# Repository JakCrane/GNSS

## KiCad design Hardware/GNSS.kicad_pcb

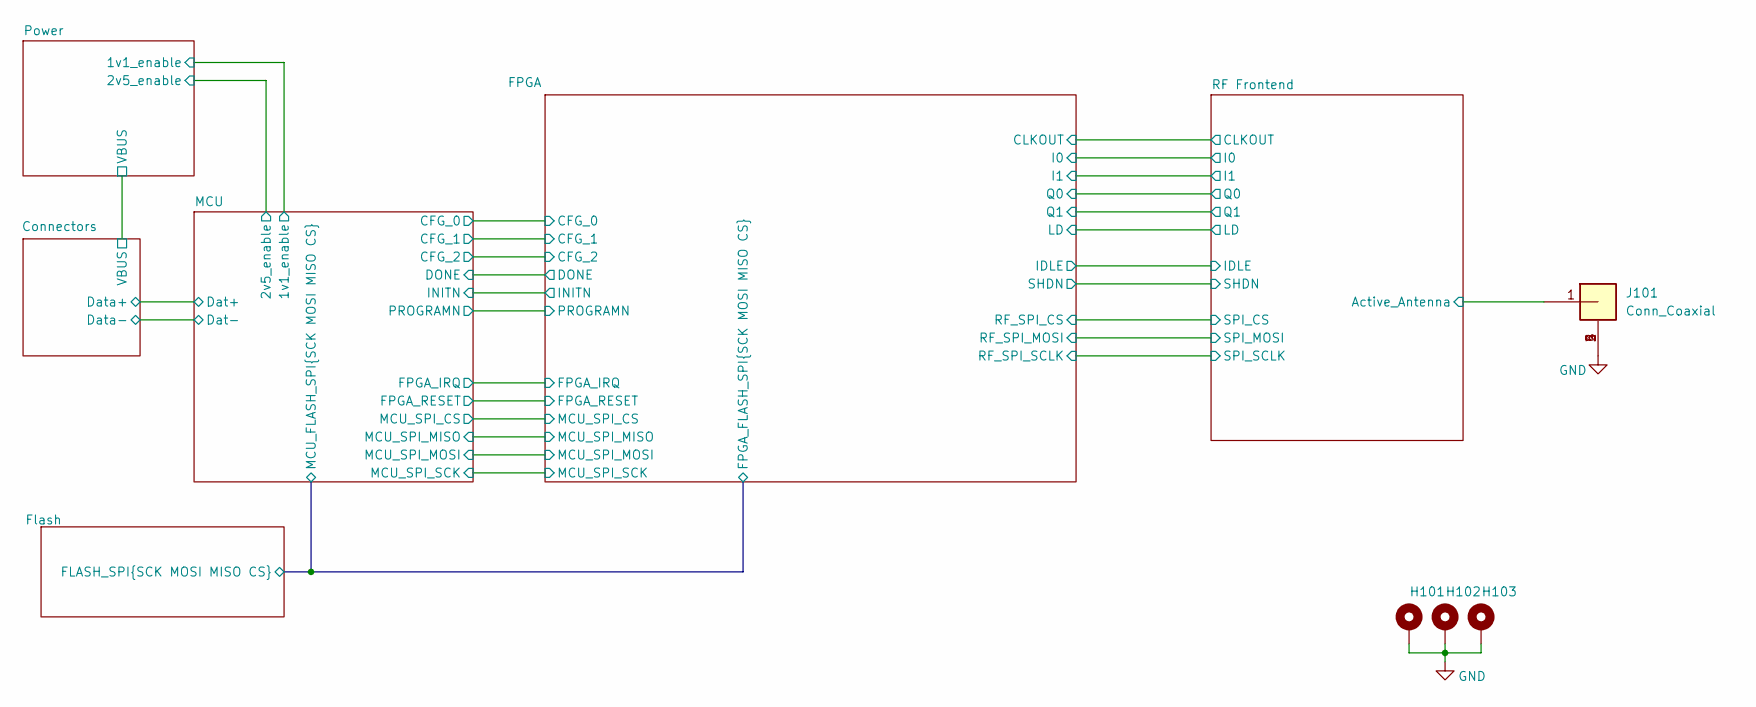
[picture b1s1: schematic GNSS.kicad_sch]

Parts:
H101, H102, H103: MountingHole_Pad; MountingHole_3.2mm_M3_Pad
J101: Conn_Coaxial; SMACONNECTOR; Mouser Part Number 471-SMACONNECTOR

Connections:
/RF Frontend/Active_Antenna: J101.1; also elsewhere on the board
GND: H101.1 (1_1), H102.1 (1_1), H103.1 (1_1), J101.2, J101.3, J101.4, J101.5; also elsewhere on the board

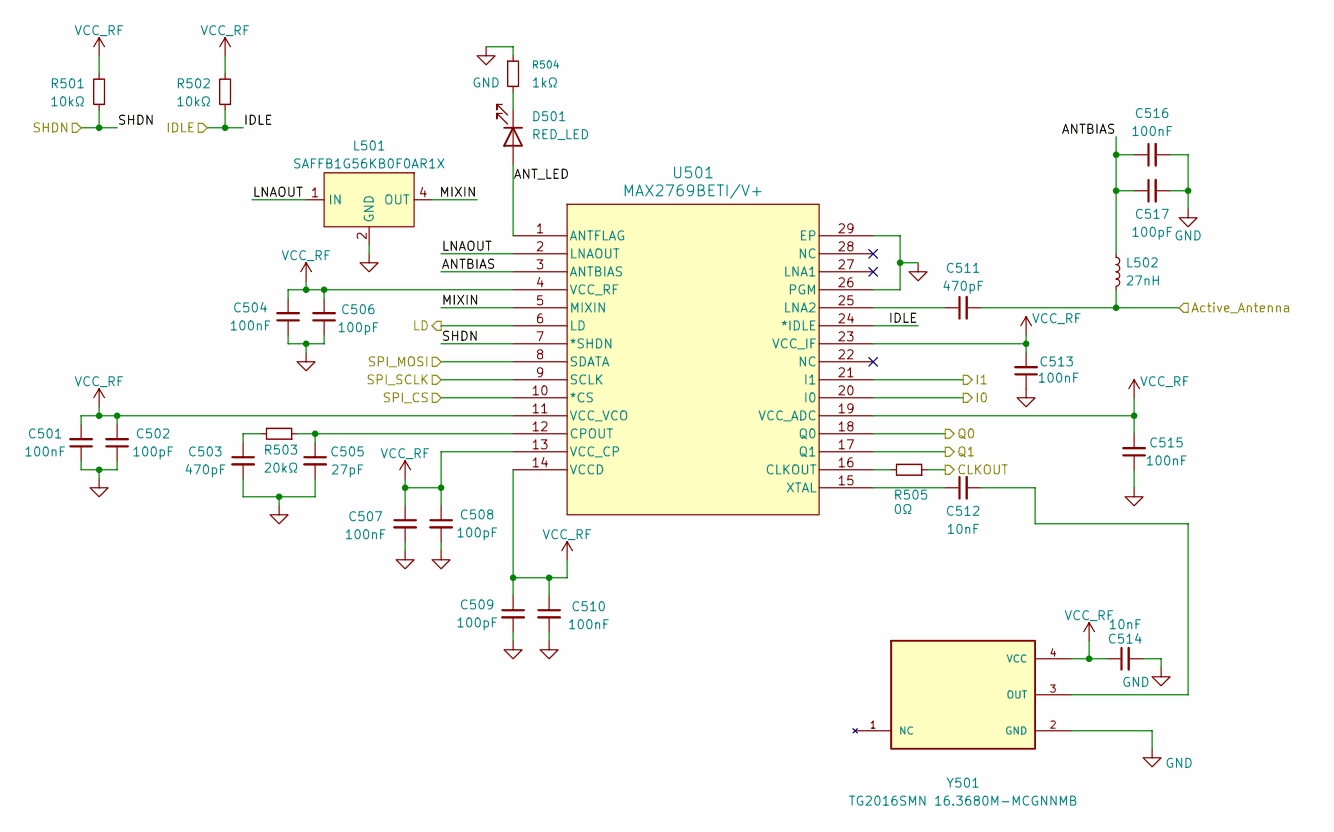
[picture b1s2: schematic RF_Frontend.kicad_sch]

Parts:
C501, C504, C507, C510, C513, C515, C516: 100nF; C_0402_1005Metric
C502, C506, C508, C509, C517: 100pF; C_0402_1005Metric
C503, C511: 470pF; C_0402_1005Metric
C505: 27pF; C_0402_1005Metric
C512, C514: 10nF; C_0402_1005Metric
D501: RED_LED; LED_0402_1005Metric
L501: SAFFB1G56KB0F0AR1X; FILTER-SMD_5P-L1.1-W0.9-L_RSFP2413E; MPN SAFFB1G56KB0F0AR1X; LCSC Part C91647
L502: 27nH; L_0402_1005Metric
R501, R502: 10kΩ; R_0402_1005Metric
R503: 20kΩ; R_0402_1005Metric
R504: 1kΩ; R_0402_1005Metric
R505: 0Ω; R_0402_1005Metric
U501: MAX2769BETI/V+; 21-0140_T2855&plus_3_MXM
Y501: TG2016SMN 16.3680M-MCGNNMB; OSC_TG2016SMN_25.0000M-ECGNNM3; PARTREV 1.3

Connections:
/FPGA/CLKOUT: R505.1; also elsewhere on the board
/FPGA/I0: U501.20 (I0); also elsewhere on the board
/FPGA/I1: U501.21 (I1); also elsewhere on the board
/FPGA/LD: U501.6 (LD); also elsewhere on the board
/FPGA/Q0: U501.18 (Q0); also elsewhere on the board
/FPGA/Q1: U501.17 (Q1); also elsewhere on the board
/FPGA/RF_SPI_CS: U501.10 (*CS); also elsewhere on the board
/FPGA/RF_SPI_MOSI: U501.8 (SDATA); also elsewhere on the board
/FPGA/RF_SPI_SCLK: U501.9 (SCLK); also elsewhere on the board
/RF Frontend/ANTBIAS: C516.1, C517.1, L502.1, U501.3 (ANTBIAS)
/RF Frontend/ANT_LED: D501.2 (A), U501.1 (ANTFLAG)
/RF Frontend/Active_Antenna: C511.2, L502.2; also elsewhere on the board
/RF Frontend/IDLE: R502.1, U501.24 (*IDLE); also elsewhere on the board
/RF Frontend/LNAOUT: L501.1 (IN), U501.2 (LNAOUT)
/RF Frontend/MIXIN: L501.4 (OUT), U501.5 (MIXIN)
/RF Frontend/SHDN: R501.1, U501.7 (*SHDN); also elsewhere on the board
GND: C501.1, C502.1, C503.2, C504.1, C505.2, C506.1, C507.2, C508.2, C509.2, C510.2, C513.1, C514.2, C515.1, C516.2, C517.2, L501.2 (GND), L501.3 (GND), L501.5 (GND), R504.1, U501.26 (PGM), U501.29 (EP), Y501.2 (GND); also elsewhere on the board
unnamed: C503.1, R503.2
unnamed: D501.1 (K), R504.2
unnamed: R505.2, U501.16 (CLKOUT)
unnamed: C505.1, R503.1, U501.12 (CPOUT)
unnamed: C511.1, U501.25 (LNA2)
unnamed: C512.1, U501.15 (XTAL)
unnamed: C512.2, Y501.3 (OUT)
VCC_RF: C501.2, C502.2, C504.2, C506.2, C507.1, C508.1, C509.1, C510.1, C513.2, C514.1, C515.2, R501.2, R502.2, U501.4 (VCC_RF), U501.11 (VCC_VCO), U501.13 (VCC_CP), U501.14 (VCCD), U501.19 (VCC_ADC), U501.23 (VCC_IF), Y501.4 (VCC); also elsewhere on the board

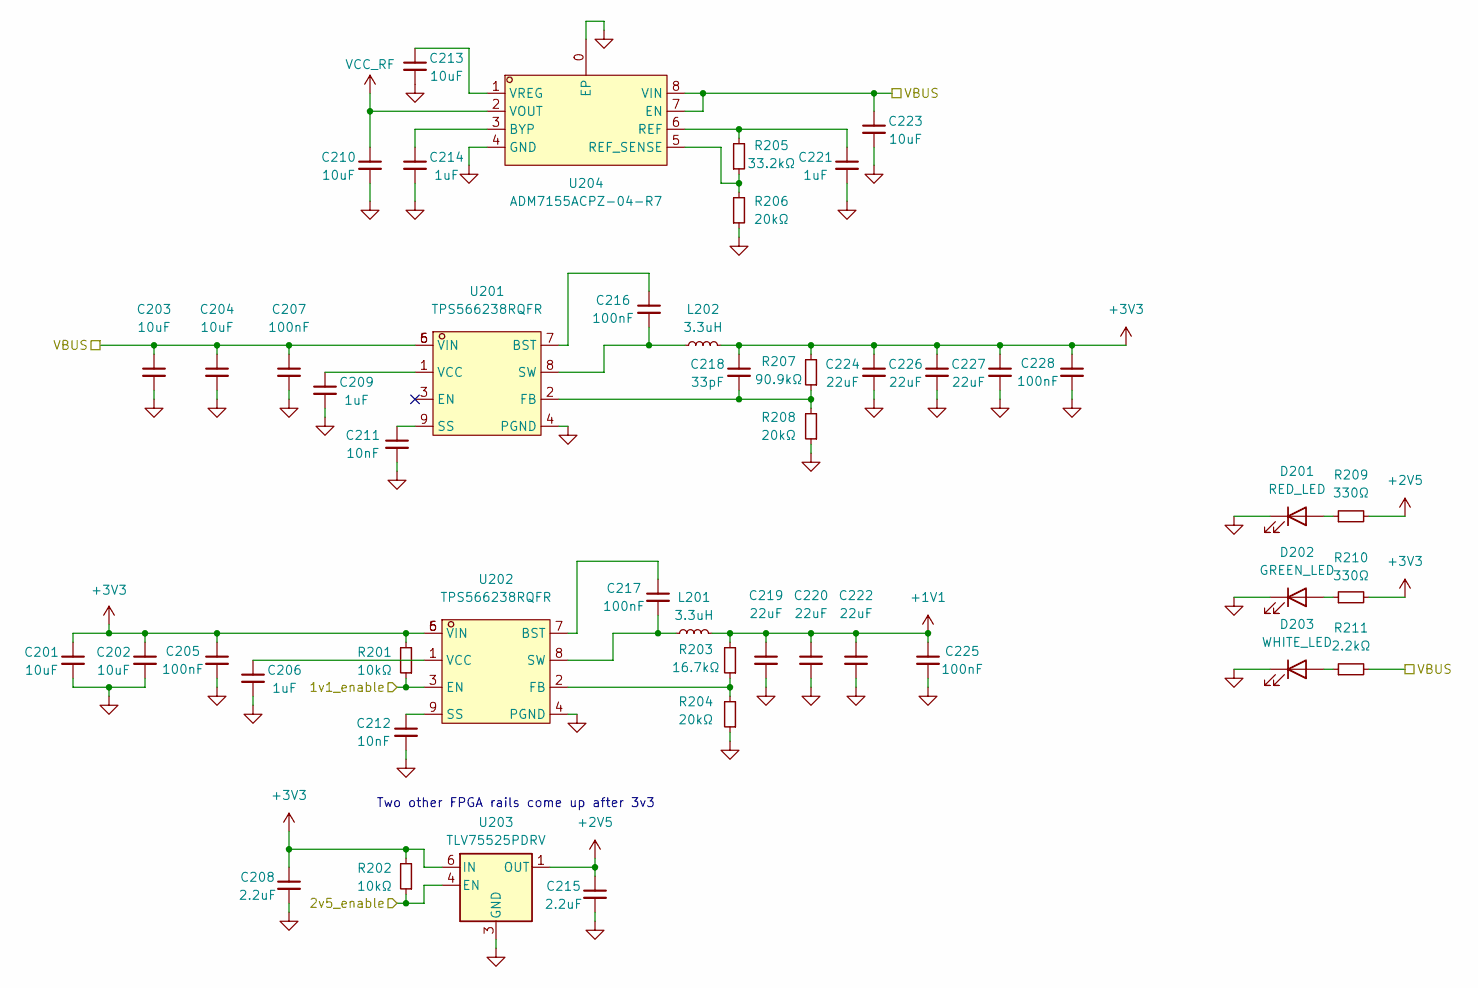
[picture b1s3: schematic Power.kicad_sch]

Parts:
C201, C202, C203, C204, C210, C213, C223: 10uF; C_0805_2012Metric
C205, C207, C216, C217, C225, C228: 100nF; C_0402_1005Metric
C206, C209, C214, C221: 1uF; C_0402_1005Metric
C208, C215: 2.2uF; C_0603_1608Metric
C211, C212: 10nF; C_0402_1005Metric
C218: 33pF; C_0402_1005Metric
C219, C220, C222, C224, C226, C227: 22uF; C_1210_3225Metric
D201: RED_LED; LED_0402_1005Metric
D202: GREEN_LED; LED_0402_1005Metric
D203: WHITE_LED; LED_0402_1005Metric
L201, L202: 3.3uH; L_Wurth_WE-HEPA-5030
R201, R202: 10kΩ; R_0402_1005Metric
R203: 16.7kΩ; R_0402_1005Metric
R204, R206, R208: 20kΩ; R_0402_1005Metric
R205: 33.2kΩ; R_0402_1005Metric
R207: 90.9kΩ; R_0402_1005Metric
R209, R210: 330Ω; R_0402_1005Metric
R211: 2.2kΩ; R_0402_1005Metric
U201, U202: TPS566238RQFR; VQFN-HR-9_2.0-W1.5-P0.5-TL_TI_RQF0009A; MPN TPS566238RQFR; LCSC Part C5219353
U203: TLV75525PDRV; WSON-6-1EP_2x2mm_P0.65mm_EP1x1.6mm
U204: ADM7155ACPZ-04-R7; LFCSP-8_L3.0-W3.0-P0.50-BL-EP; MPN ADM7155ACPZ-04-R7; LCSC Part C209548

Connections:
+1V1: C219.1, C220.1, C222.1, C225.1, L201.2, R203.2; also elsewhere on the board
+2V5: C215.1, R209.2, U203.1 (OUT); also elsewhere on the board
+3V3: C201.1, C202.1, C205.1, C208.1, C218.1, C224.1, C226.1, C227.1, C228.1, L202.2, R201.2, R202.2, R207.2, R210.2, U202.5 (VIN), U202.6 (VIN), U203.6 (IN); also elsewhere on the board
/Connectors/VBUS: C203.1, C204.1, C207.1, C223.1, R211.2, U201.5 (VIN), U201.6 (VIN), U204.7 (EN), U204.8 (VIN); also elsewhere on the board
/MCU/1v1_enable: R201.1, U202.3 (EN); also elsewhere on the board
/MCU/2v5_enable: R202.1, U203.4 (EN); also elsewhere on the board
GND: C201.2, C202.2, C203.2, C204.2, C205.2, C206.2, C207.2, C208.2, C209.2, C210.2, C211.2, C212.2, C213.2, C214.2, C215.2, C219.2, C220.2, C221.2, C222.2, C223.2, C224.2, C225.2, C226.2, C227.2, C228.2, D201.1 (K), D202.1 (K), D203.1 (K), R204.1, R206.1, R208.1, U201.4 (PGND), U202.4 (PGND), U203.2 (NC), U203.3 (GND), U203.5 (NC), U203.7 (GND), U204.0 (EP), U204.4 (GND); also elsewhere on the board
unnamed: D201.2 (A), R209.1
unnamed: D202.2 (A), R210.1
unnamed: D203.2 (A), R211.1
unnamed: C216.1, U201.7 (BST)
unnamed: C218.2, R207.1, R208.2, U201.2 (FB)
unnamed: C211.1, U201.9 (SS)
unnamed: C216.2, L202.1, U201.8 (SW)
unnamed: C209.1, U201.1 (VCC)
unnamed: C217.1, U202.7 (BST)
unnamed: R203.1, R204.2, U202.2 (FB)
unnamed: C212.1, U202.9 (SS)
unnamed: C217.2, L201.1, U202.8 (SW)
unnamed: C206.1, U202.1 (VCC)
unnamed: C214.1, U204.3 (BYP)
unnamed: C221.1, R205.2, U204.6 (REF)
unnamed: R205.1, R206.2, U204.5 (REF_SENSE)
unnamed: C213.1, U204.1 (VREG)
VCC_RF: C210.1, U204.2 (VOUT); also elsewhere on the board

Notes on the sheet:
Two other FPGA rails come up after 3v3

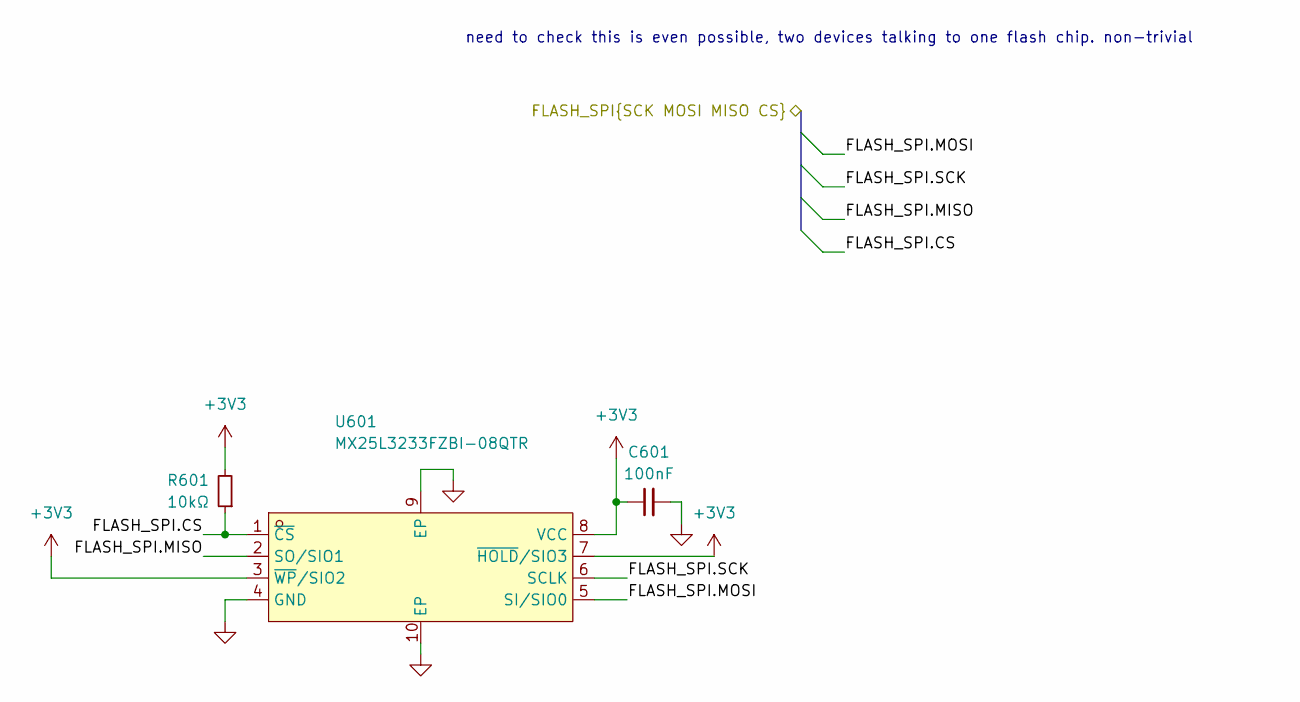
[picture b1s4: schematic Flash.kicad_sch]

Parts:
C601: 100nF; C_0402_1005Metric
R601: 10kΩ; R_0402_1005Metric
U601: MX25L3233FZBI-08QTR; USON-8_L4.0-W3.0-P0.80-BL_IS25WP032D; MPN MX25L3233FZBI-08QTR; LCSC Part C2803002

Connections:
+3V3: C601.1, R601.2, U601.3 (~WP/SIO2), U601.7 (~HOLD/SIO3), U601.8 (VCC); also elsewhere on the board
/FPGA/FPGA_FLASH_SPI.CS: R601.1, U601.1 (~CS); also elsewhere on the board
/FPGA/FPGA_FLASH_SPI.MISO: U601.2 (SO/SIO1); also elsewhere on the board
/FPGA/FPGA_FLASH_SPI.MOSI: U601.5 (SI/SIO0); also elsewhere on the board
/FPGA/FPGA_FLASH_SPI.SCK: U601.6 (SCLK); also elsewhere on the board
GND: C601.2, U601.4 (GND), U601.9 (EP), U601.10 (EP); also elsewhere on the board

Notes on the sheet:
need to check this is even possible, two devices talking to one flash chip. non-trivial

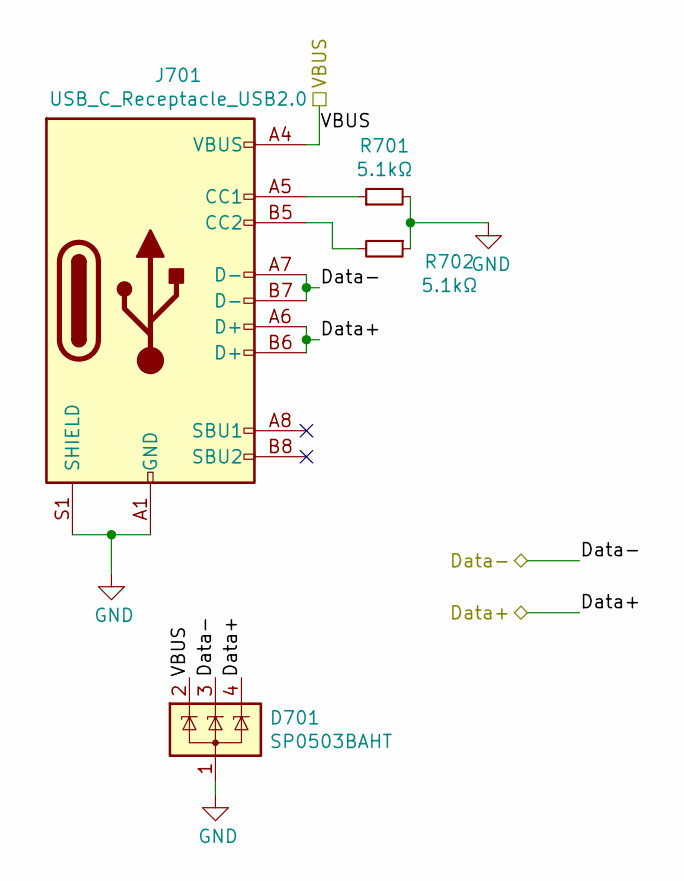
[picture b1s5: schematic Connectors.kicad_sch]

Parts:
D701: SP0503BAHT; SOT-143
J701: USB_C_Receptacle_USB2.0; USB_C_Receptacle_Palconn_UTC16-G
R701, R702: 5.1kΩ; R_0402_1005Metric

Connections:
/Connectors/Data+: D701.4 (K), J701.A6 (D+), J701.B6 (D+); also elsewhere on the board
/Connectors/Data-: D701.3 (K), J701.A7 (D-), J701.B7 (D-); also elsewhere on the board
/Connectors/VBUS: D701.2 (K), J701.A4 (VBUS), J701.A9 (VBUS), J701.B4 (VBUS), J701.B9 (VBUS); also elsewhere on the board
GND: D701.1 (A), J701.A1 (GND), J701.A12 (GND), J701.B1 (GND), J701.B12 (GND), J701.S1 (SHIELD), R701.2, R702.1; also elsewhere on the board
unnamed: J701.A5 (CC1), R701.1
unnamed: J701.B5 (CC2), R702.2

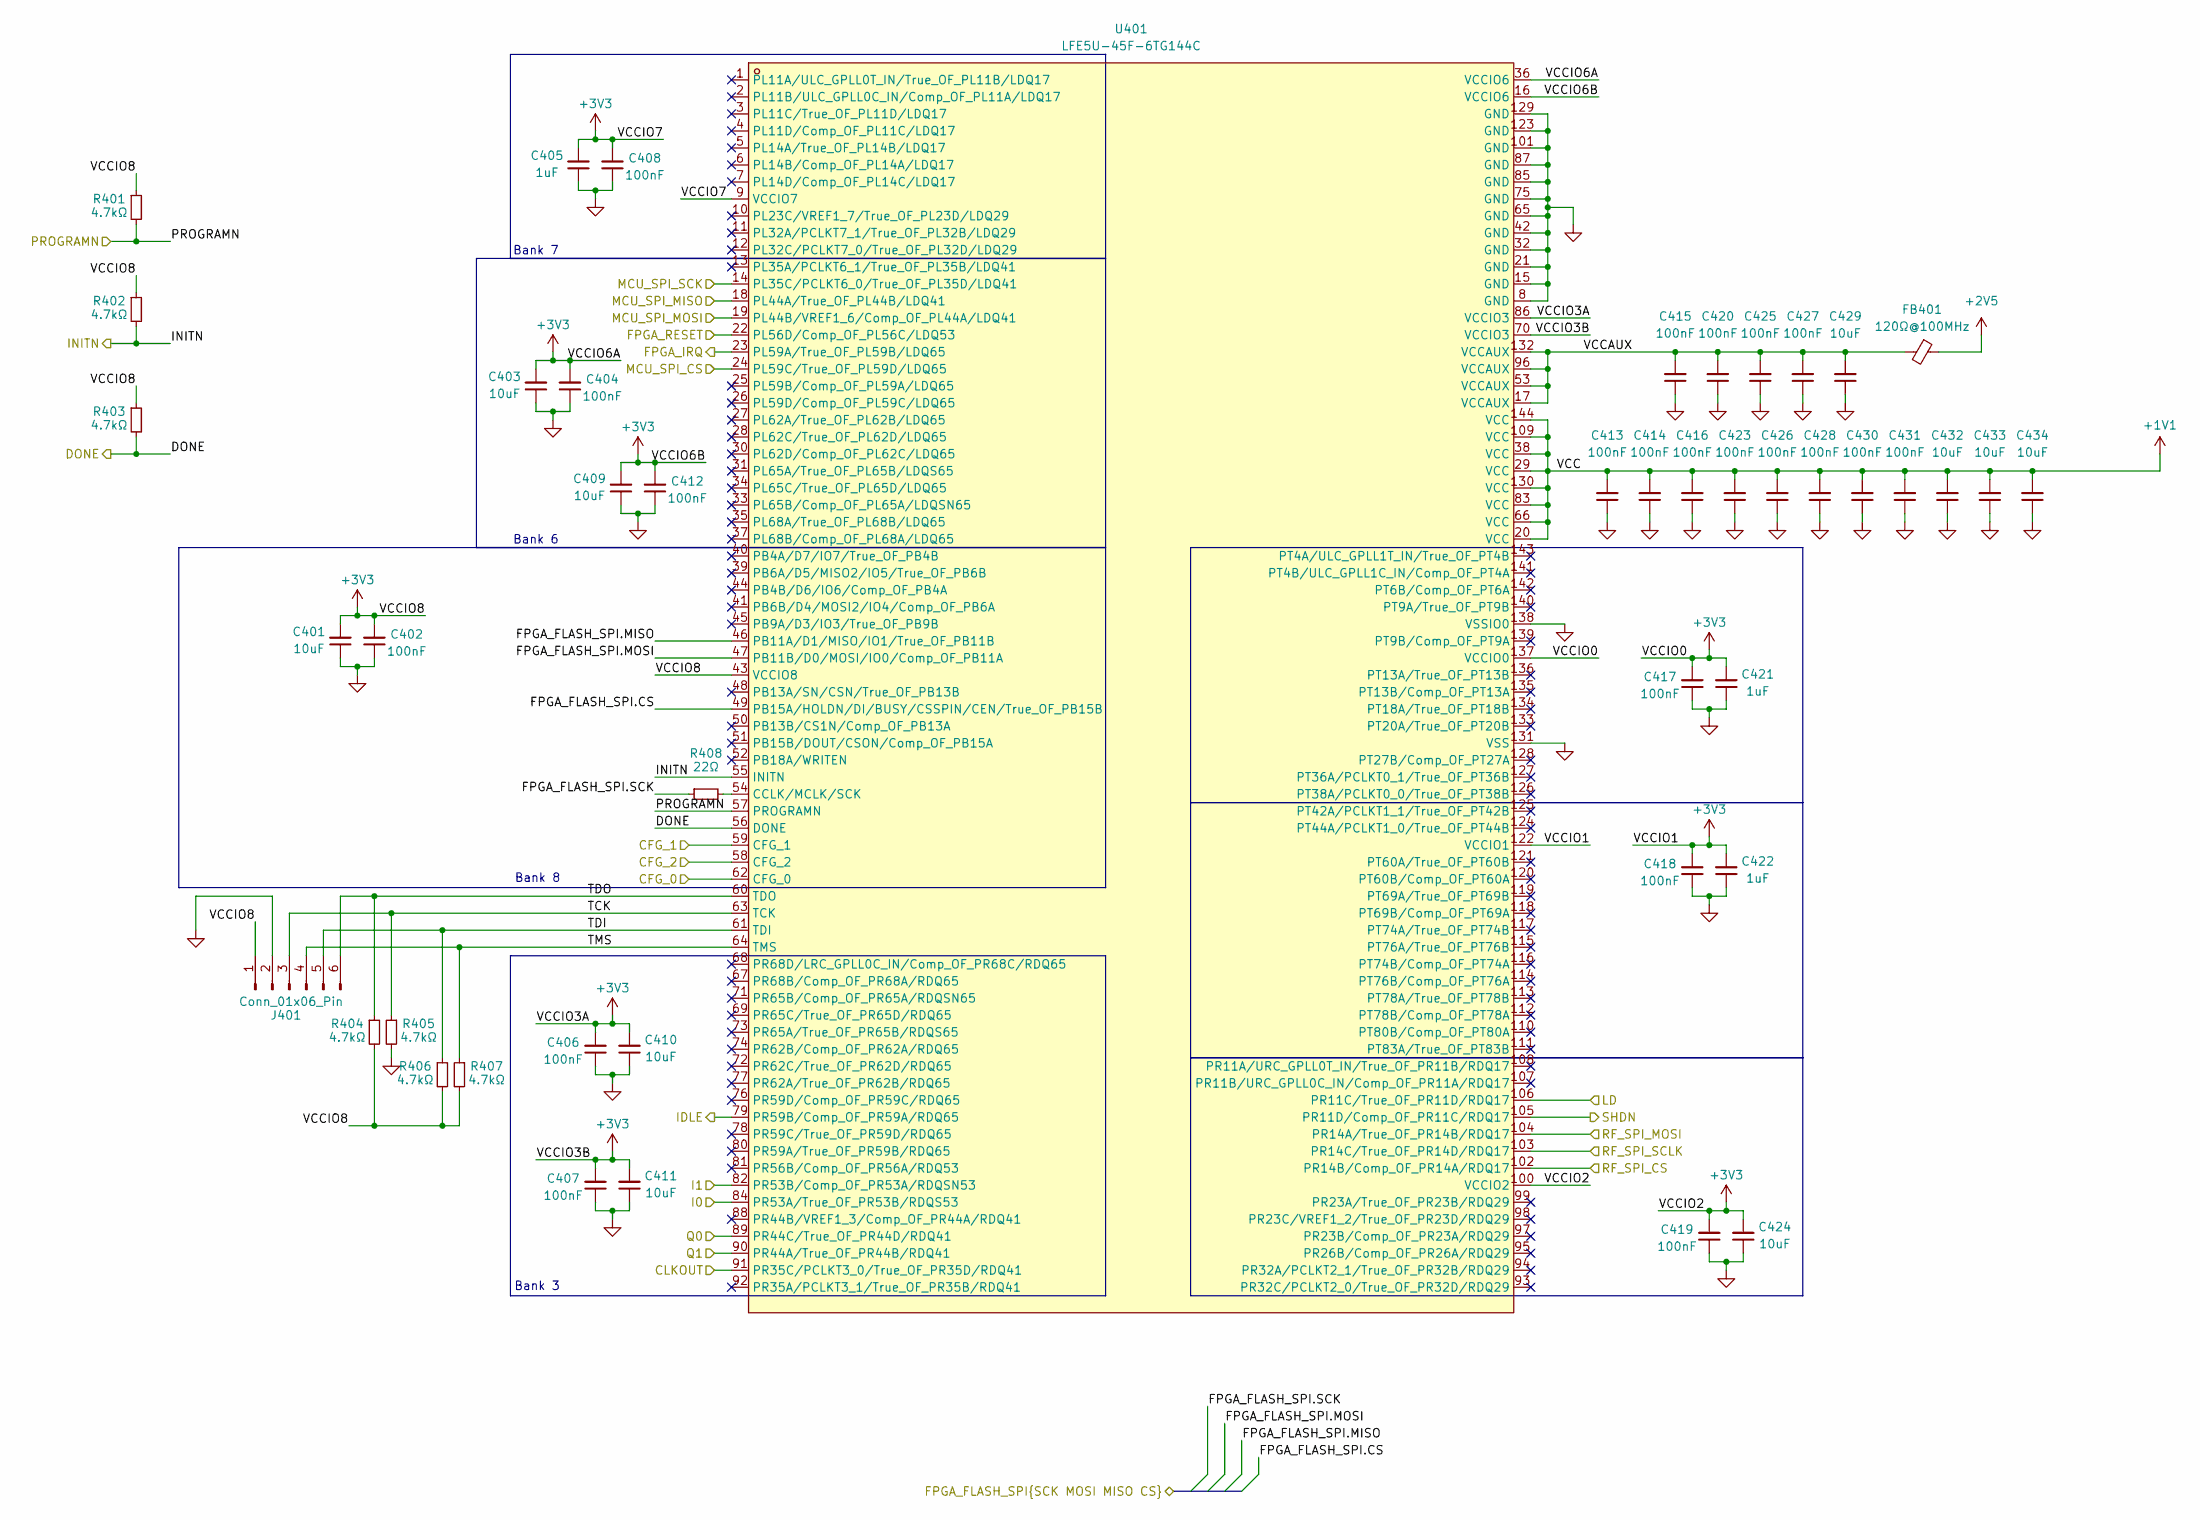
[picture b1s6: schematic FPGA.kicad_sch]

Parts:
C401, C403, C409, C410, C411, C424, C429, C432, C433, C434: 10uF; C_0805_2012Metric
C402, C404, C406, C407, C408, C412, C413, C414, C415, C416, C417, C418, C419, C420, C423, C425, C426, C427, C428, C430, C431: 100nF; C_0402_1005Metric
C405, C421, C422: 1uF; C_0402_1005Metric
FB401: 120Ω@100MHz; L_0603_1608Metric
J401: Conn_01x06_Pin; Molex_Nano-Fit_105313-xx06_1x06_P2.50mm_Horizontal
R401, R402, R403, R404, R405, R406, R407: 4.7kΩ; R_0402_1005Metric
R408: 22Ω; R_0402_1005Metric
U401: LFE5U-45F-6TG144C; TQFP-144_L20.0-W20.0-P0.50-LS22.0-TL; MPN LFE5U-45F-6TG144C; LCSC Part C19979193

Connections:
+1V1: C413.2, C414.2, C416.2, C423.2, C426.2, C428.2, C430.2, C431.2, C432.2, C433.2, C434.2, U401.20 (VCC), U401.29 (VCC), U401.38 (VCC), U401.66 (VCC), U401.83 (VCC), U401.109 (VCC), U401.130 (VCC), U401.144 (VCC); also elsewhere on the board
+2V5: FB401.1; also elsewhere on the board
+3V3: C401.2, C402.2, C403.2, C404.2, C405.2, C406.2, C407.2, C408.2, C409.2, C410.2, C411.2, C412.2, C417.2, C418.2, C419.2, C421.2, C422.2, C424.2, J401.1, R401.1, R402.1, R403.1, R404.2, R406.2, R407.2, U401.9 (VCCIO7), U401.16 (VCCIO6), U401.36 (VCCIO6), U401.43 (VCCIO8), U401.70 (VCCIO3), U401.86 (VCCIO3), U401.100 (VCCIO2), U401.122 (VCCIO1), U401.137 (VCCIO0); also elsewhere on the board
/FPGA/CFG_0: U401.62 (CFG_0); also elsewhere on the board
/FPGA/CFG_1: U401.59 (CFG_1); also elsewhere on the board
/FPGA/CFG_2: U401.58 (CFG_2); also elsewhere on the board
/FPGA/CLKOUT: U401.91 (PR35C/PCLKT3_0/True_OF_PR35D/RDQ41); also elsewhere on the board
/FPGA/DONE: R403.2, U401.56 (DONE); also elsewhere on the board
/FPGA/FPGA_FLASH_SPI.CS: U401.49 (PB15A/HOLDN/DI/BUSY/CSSPIN/CEN/True_OF_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); also elsewhere on the board
/FPGA/FPGA_FLASH_SPI.MISO: U401.46 (PB11A/D1/MISO/IO1/True_OF_PB11B); also elsewhere on the board
/FPGA/FPGA_FLASH_SPI.MOSI: U401.47 (PB11B/D0/MOSI/IO0/Comp_OF_PB11A); also elsewhere on the board
/FPGA/FPGA_FLASH_SPI.SCK: R408.1; also elsewhere on the board
/FPGA/FPGA_IRQ: U401.23 (PL59A/True_OF_PL59B/LDQ65); also elsewhere on the board
/FPGA/FPGA_RESET: U401.22 (PL56D/Comp_OF_PL56C/LDQ53); also elsewhere on the board
/FPGA/I0: U401.84 (PR53A/True_OF_PR53B/RDQS53); also elsewhere on the board
/FPGA/I1: U401.82 (PR53B/Comp_OF_PR53A/RDQSN53); also elsewhere on the board
/FPGA/INITN: R402.2, U401.55 (INITN); also elsewhere on the board
/FPGA/LD: U401.106 (PR11C/True_OF_PR11D/RDQ17); also elsewhere on the board
/FPGA/MCU_SPI_CS: U401.24 (PL59C/True_OF_PL59D/LDQ65); also elsewhere on the board
/FPGA/MCU_SPI_MISO: U401.18 (PL44A/True_OF_PL44B/LDQ41); also elsewhere on the board
/FPGA/MCU_SPI_MOSI: U401.19 (PL44B/VREF1_6/Comp_OF_PL44A/LDQ41); also elsewhere on the board
/FPGA/MCU_SPI_SCK: U401.14 (PL35C/PCLKT6_0/True_OF_PL35D/LDQ41); also elsewhere on the board
/FPGA/PROGRAMN: R401.2, U401.57 (PROGRAMN); also elsewhere on the board
/FPGA/Q0: U401.89 (PR44C/True_OF_PR44D/RDQ41); also elsewhere on the board
/FPGA/Q1: U401.90 (PR44A/True_OF_PR44B/RDQ41); also elsewhere on the board
/FPGA/RF_SPI_CS: U401.102 (PR14B/Comp_OF_PR14A/RDQ17); also elsewhere on the board
/FPGA/RF_SPI_MOSI: U401.104 (PR14A/True_OF_PR14B/RDQ17); also elsewhere on the board
/FPGA/RF_SPI_SCLK: U401.103 (PR14C/True_OF_PR14D/RDQ17); also elsewhere on the board
/FPGA/TCK: J401.3, R405.1, U401.63 (TCK)
/FPGA/TDI: J401.5, R406.1, U401.61 (TDI)
/FPGA/TDO: J401.6, R404.1, U401.60 (TDO)
/FPGA/TMS: J401.4, R407.1, U401.64 (TMS)
/FPGA/VCCAUX: C415.2, C420.2, C425.2, C427.2, C429.2, FB401.2, U401.17 (VCCAUX), U401.53 (VCCAUX), U401.96 (VCCAUX), U401.132 (VCCAUX)
/RF Frontend/IDLE: U401.79 (PR59B/Comp_OF_PR59A/RDQ65); also elsewhere on the board
/RF Frontend/SHDN: U401.105 (PR11D/Comp_OF_PR11C/RDQ17); also elsewhere on the board
GND: C401.1, C402.1, C403.1, C404.1, C405.1, C406.1, C407.1, C408.1, C409.1, C410.1, C411.1, C412.1, C413.1, C414.1, C415.1, C416.1, C417.1, C418.1, C419.1, C420.1, C421.1, C422.1, C423.1, C424.1, C425.1, C426.1, C427.1, C428.1, C429.1, C430.1, C431.1, C432.1, C433.1, C434.1, J401.2, R405.2, U401.8 (GND), U401.15 (GND), U401.21 (GND), U401.32 (GND), U401.42 (GND), U401.65 (GND), U401.75 (GND), U401.85 (GND), U401.87 (GND), U401.101 (GND), U401.123 (GND), U401.129 (GND), U401.131 (VSS), U401.138 (VSSIO0); also elsewhere on the board
unnamed: R408.2, U401.54 (CCLK/MCLK/SCK)

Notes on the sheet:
Bank 3
Bank 8
Bank 6
Bank 7

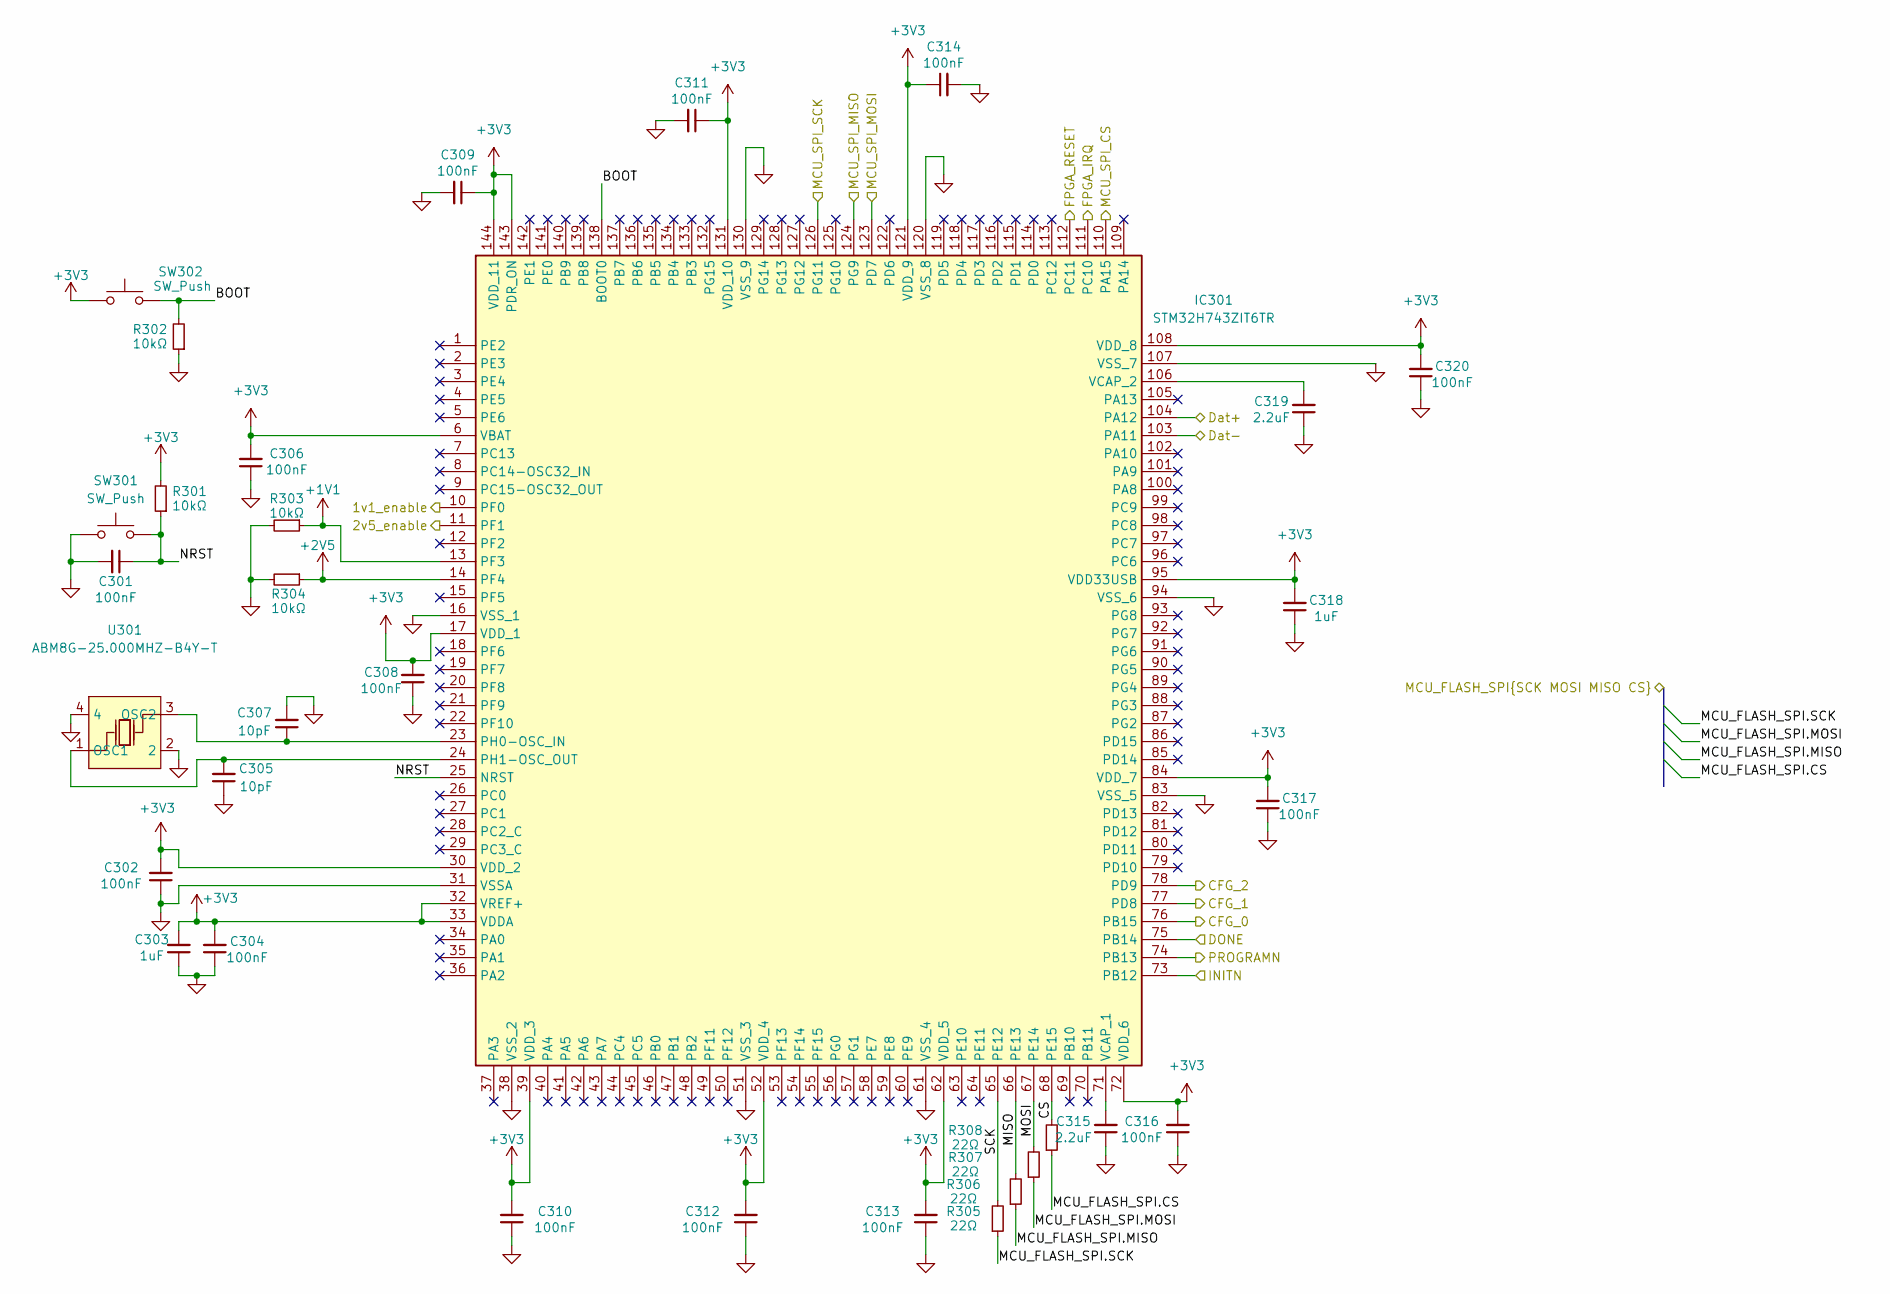
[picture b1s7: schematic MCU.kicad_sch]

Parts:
C301, C302, C304, C306, C308, C309, C310, C311, C312, C313, C314, C316, C317, C320: 100nF; C_0402_1005Metric
C303, C318: 1uF; C_0402_1005Metric
C305, C307: 10pF; C_0402_1005Metric
C315, C319: 2.2uF; C_0603_1608Metric
IC301: STM32H743ZIT6TR; QFP50P2200X2200X160-144N; Mouser Part Number 511-STM32H743ZIT6TR
R301, R302, R303, R304: 10kΩ; R_0402_1005Metric
R305, R306, R307, R308: 22Ω; R_0402_1005Metric
SW301, SW302: SW_Push; PinHeader_1x02_P2.54mm_Vertical
U301: ABM8G-25.000MHZ-B4Y-T; CRYSTAL-SMD_4P-L3.2-W2.5-TR; MPN ABM8G-25.000MHZ-B4Y-T; LCSC Part C596913

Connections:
+1V1: IC301.13 (PF3), R303.1; also elsewhere on the board
+2V5: IC301.14 (PF4), R304.1; also elsewhere on the board
+3V3: C302.2, C303.2, C304.2, C306.2, C308.2, C309.1, C310.2, C311.1, C312.2, C313.2, C314.1, C316.2, C317.2, C318.2, C320.2, IC301.6 (VBAT), IC301.17 (VDD_1), IC301.30 (VDD_2), IC301.32 (VREF+), IC301.33 (VDDA), IC301.39 (VDD_3), IC301.52 (VDD_4), IC301.62 (VDD_5), IC301.72 (VDD_6), IC301.84 (VDD_7), IC301.95 (VDD33USB), IC301.108 (VDD_8), IC301.121 (VDD_9), IC301.131 (VDD_10), IC301.143 (PDR_ON), IC301.144 (VDD_11), R301.2, SW302.1; also elsewhere on the board
/Connectors/Data+: IC301.104 (PA12); also elsewhere on the board
/Connectors/Data-: IC301.103 (PA11); also elsewhere on the board
/FPGA/CFG_0: IC301.76 (PB15); also elsewhere on the board
/FPGA/CFG_1: IC301.77 (PD8); also elsewhere on the board
/FPGA/CFG_2: IC301.78 (PD9); also elsewhere on the board
/FPGA/DONE: IC301.75 (PB14); also elsewhere on the board
/FPGA/FPGA_FLASH_SPI.CS: R308.1; also elsewhere on the board
/FPGA/FPGA_FLASH_SPI.MISO: R306.1; also elsewhere on the board
/FPGA/FPGA_FLASH_SPI.MOSI: R307.1; also elsewhere on the board
/FPGA/FPGA_FLASH_SPI.SCK: R305.1; also elsewhere on the board
/FPGA/FPGA_IRQ: IC301.111 (PC10); also elsewhere on the board
/FPGA/FPGA_RESET: IC301.112 (PC11); also elsewhere on the board
/FPGA/INITN: IC301.73 (PB12); also elsewhere on the board
/FPGA/MCU_SPI_CS: IC301.110 (PA15); also elsewhere on the board
/FPGA/MCU_SPI_MISO: IC301.124 (PG9); also elsewhere on the board
/FPGA/MCU_SPI_MOSI: IC301.123 (PD7); also elsewhere on the board
/FPGA/MCU_SPI_SCK: IC301.126 (PG11); also elsewhere on the board
/FPGA/PROGRAMN: IC301.74 (PB13); also elsewhere on the board
/MCU/1v1_enable: IC301.10 (PF0); also elsewhere on the board
/MCU/2v5_enable: IC301.11 (PF1); also elsewhere on the board
/MCU/BOOT: IC301.138 (BOOT0), R302.2, SW302.2
/MCU/CS: IC301.68 (PE15), R308.2
/MCU/MISO: IC301.66 (PE13), R306.2
/MCU/MOSI: IC301.67 (PE14), R307.2
/MCU/NRST: C301.1, IC301.25 (NRST), R301.1, SW301.2
/MCU/SCK: IC301.65 (PE12), R305.2
GND: C301.2, C302.1, C303.1, C304.1, C305.1, C306.1, C307.2, C308.1, C309.2, C310.1, C311.2, C312.1, C313.1, C314.2, C315.1, C316.1, C317.1, C318.1, C319.1, C320.1, IC301.16 (VSS_1), IC301.31 (VSSA), IC301.38 (VSS_2), IC301.51 (VSS_3), IC301.61 (VSS_4), IC301.83 (VSS_5), IC301.94 (VSS_6), IC301.107 (VSS_7), IC301.120 (VSS_8), IC301.130 (VSS_9), R302.1, R303.2, R304.2, SW301.1, U301.2, U301.4; also elsewhere on the board
unnamed: C307.1, IC301.23 (PH0-OSC_IN), U301.3 (OSC2)
unnamed: C305.2, IC301.24 (PH1-OSC_OUT), U301.1 (OSC1)
unnamed: C315.2, IC301.71 (VCAP_1)
unnamed: C319.2, IC301.106 (VCAP_2)
